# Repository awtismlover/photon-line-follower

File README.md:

<h1 align="center"> Photon1.0: Turbo Line Follower Robot</h1>

<div align="center">

<i>Loved the project? Please consider giving a Star ⭐️</i>

</div>

## ⭐️For now work in progres⭐️

> ### **Photon will be fast and light line follower robot with track optimalization.**

## Custom ESC

> ### **For the drive system Photon will use BLDC motors which will be driven by ESCs based on Escape32**

<div align="center">
  
</div>

## Hardware

- uC - STM32G474RET6
- drivers - Custom ESCs
- sensor - 12x KTIR0711S
- battery - 300mAh 3s LiPo
- wheels - Kyosho Mini Z
- motors - 1404 BLDC
- Bluetooth - HC-04

## Credits
> Photon uses custom BLDC based on neoxic's ESCape32 project
> https://github.com/neoxic/ESCape32

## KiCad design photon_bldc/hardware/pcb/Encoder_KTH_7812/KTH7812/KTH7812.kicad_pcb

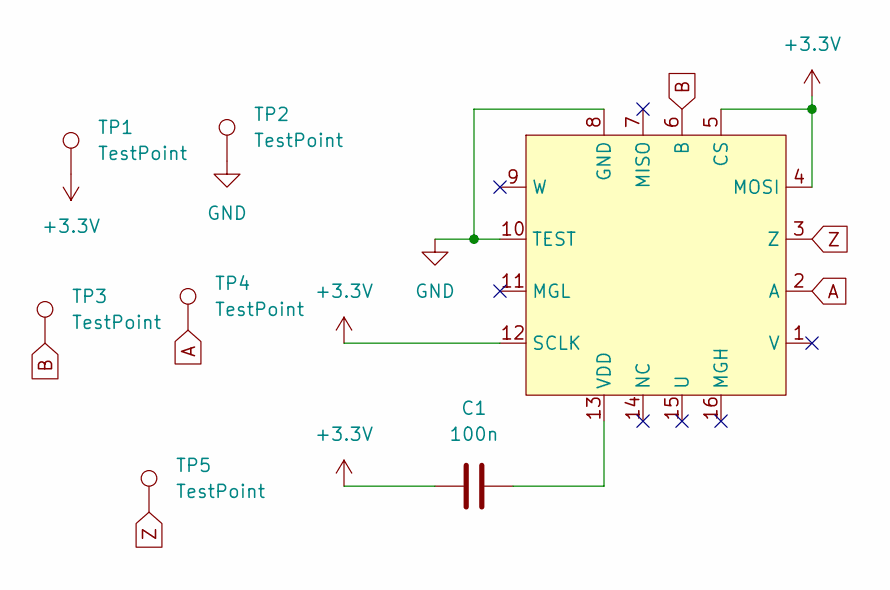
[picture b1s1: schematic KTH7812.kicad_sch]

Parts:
C1: 100n; C_0402_1005Metric
TP1, TP2, TP3, TP4, TP5: TestPoint; TestPoint_Pad_1.0x1.0mm
U1: KTH7812

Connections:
+3.3V: C1.1, TP1.1, U1.4 (MOSI), U1.5 (CS), U1.12 (SCLK)
A: TP4.1, U1.2 (A)
B: TP3.1, U1.6 (B)
GND: TP2.1, U1.8 (GND), U1.10 (TEST)
unnamed: C1.2, U1.13 (VDD)
Z: TP5.1, U1.3 (Z)

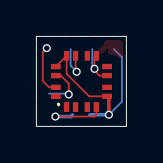
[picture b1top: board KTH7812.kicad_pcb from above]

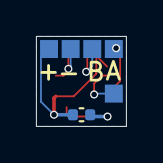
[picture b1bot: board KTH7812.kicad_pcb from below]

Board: 2 copper layers, 5.0 x 5.0 mm, 7 parts (6 on the bottom side), 6 nets.

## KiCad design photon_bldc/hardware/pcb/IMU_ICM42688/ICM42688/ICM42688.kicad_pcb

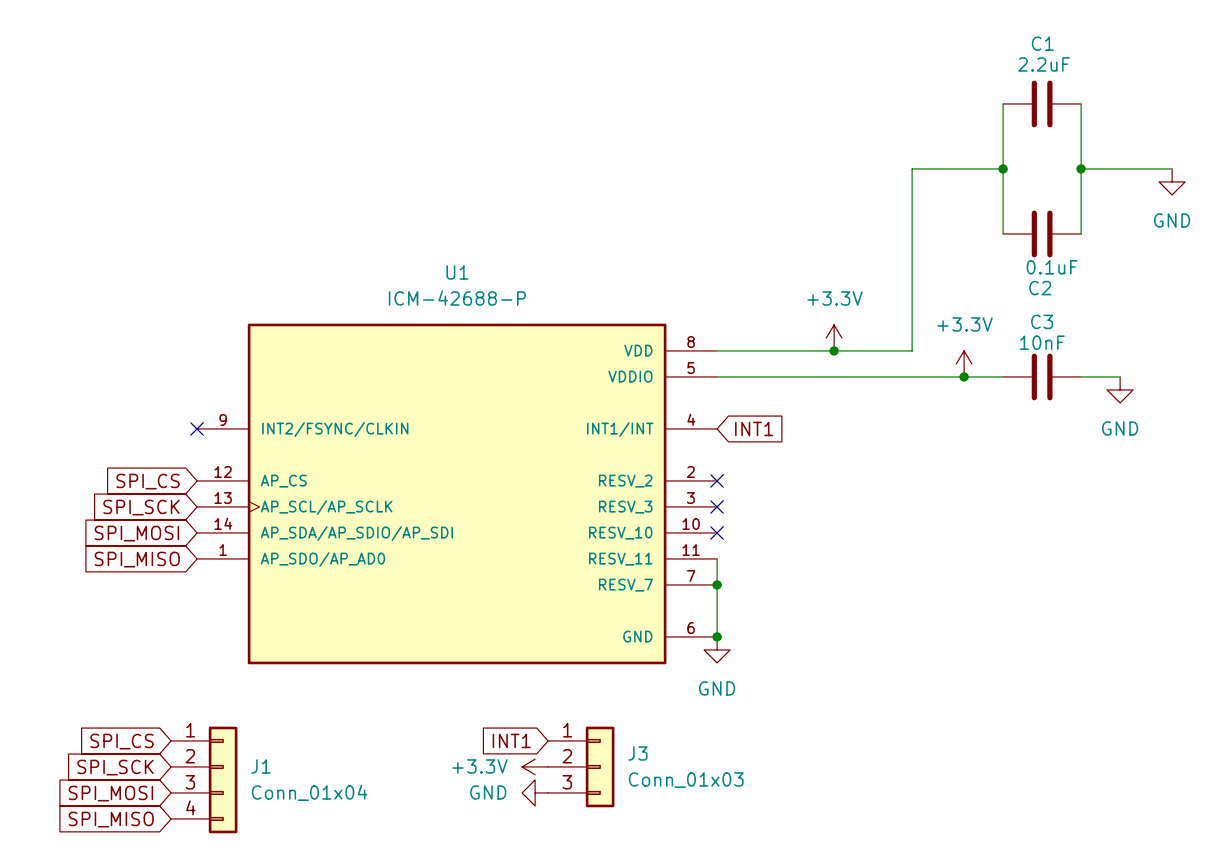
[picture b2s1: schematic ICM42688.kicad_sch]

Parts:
C1: 2.2uF; C_0402_1005Metric_Pad0.74x0.62mm_HandSolder
C2: 0.1uF; C_0402_1005Metric_Pad0.74x0.62mm_HandSolder
C3: 10nF; C_0402_1005Metric_Pad0.74x0.62mm_HandSolder
J1: Conn_01x04; 4_cable_pad
J3: Conn_01x03; 3_cable_pad
U1: ICM-42688-P; PQFN50P300X250X97-14N; PARTREV 1.2

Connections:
+3.3V: C1.2, C2.1, C3.1, J3.2, U1.5 (VDDIO), U1.8 (VDD)
GND: C1.1, C2.2, C3.2, J3.3, U1.6 (GND), U1.7 (RESV_7), U1.11 (RESV_11)
INT1: J3.1, U1.4 (INT1/INT)
SPI_CS: J1.1, U1.12 (AP_CS)
SPI_MISO: J1.4, U1.1 (AP_SDO/AP_AD0)
SPI_MOSI: J1.3, U1.14 (AP_SDA/AP_SDIO/AP_SDI)
SPI_SCK: J1.2, U1.13 (AP_SCL/AP_SCLK)

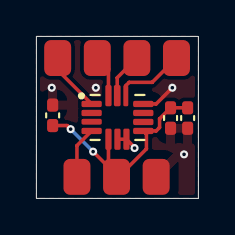
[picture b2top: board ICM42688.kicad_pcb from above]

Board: 2 copper layers, 9.0 x 9.0 mm, 6 parts (0 on the bottom side), 7 nets.

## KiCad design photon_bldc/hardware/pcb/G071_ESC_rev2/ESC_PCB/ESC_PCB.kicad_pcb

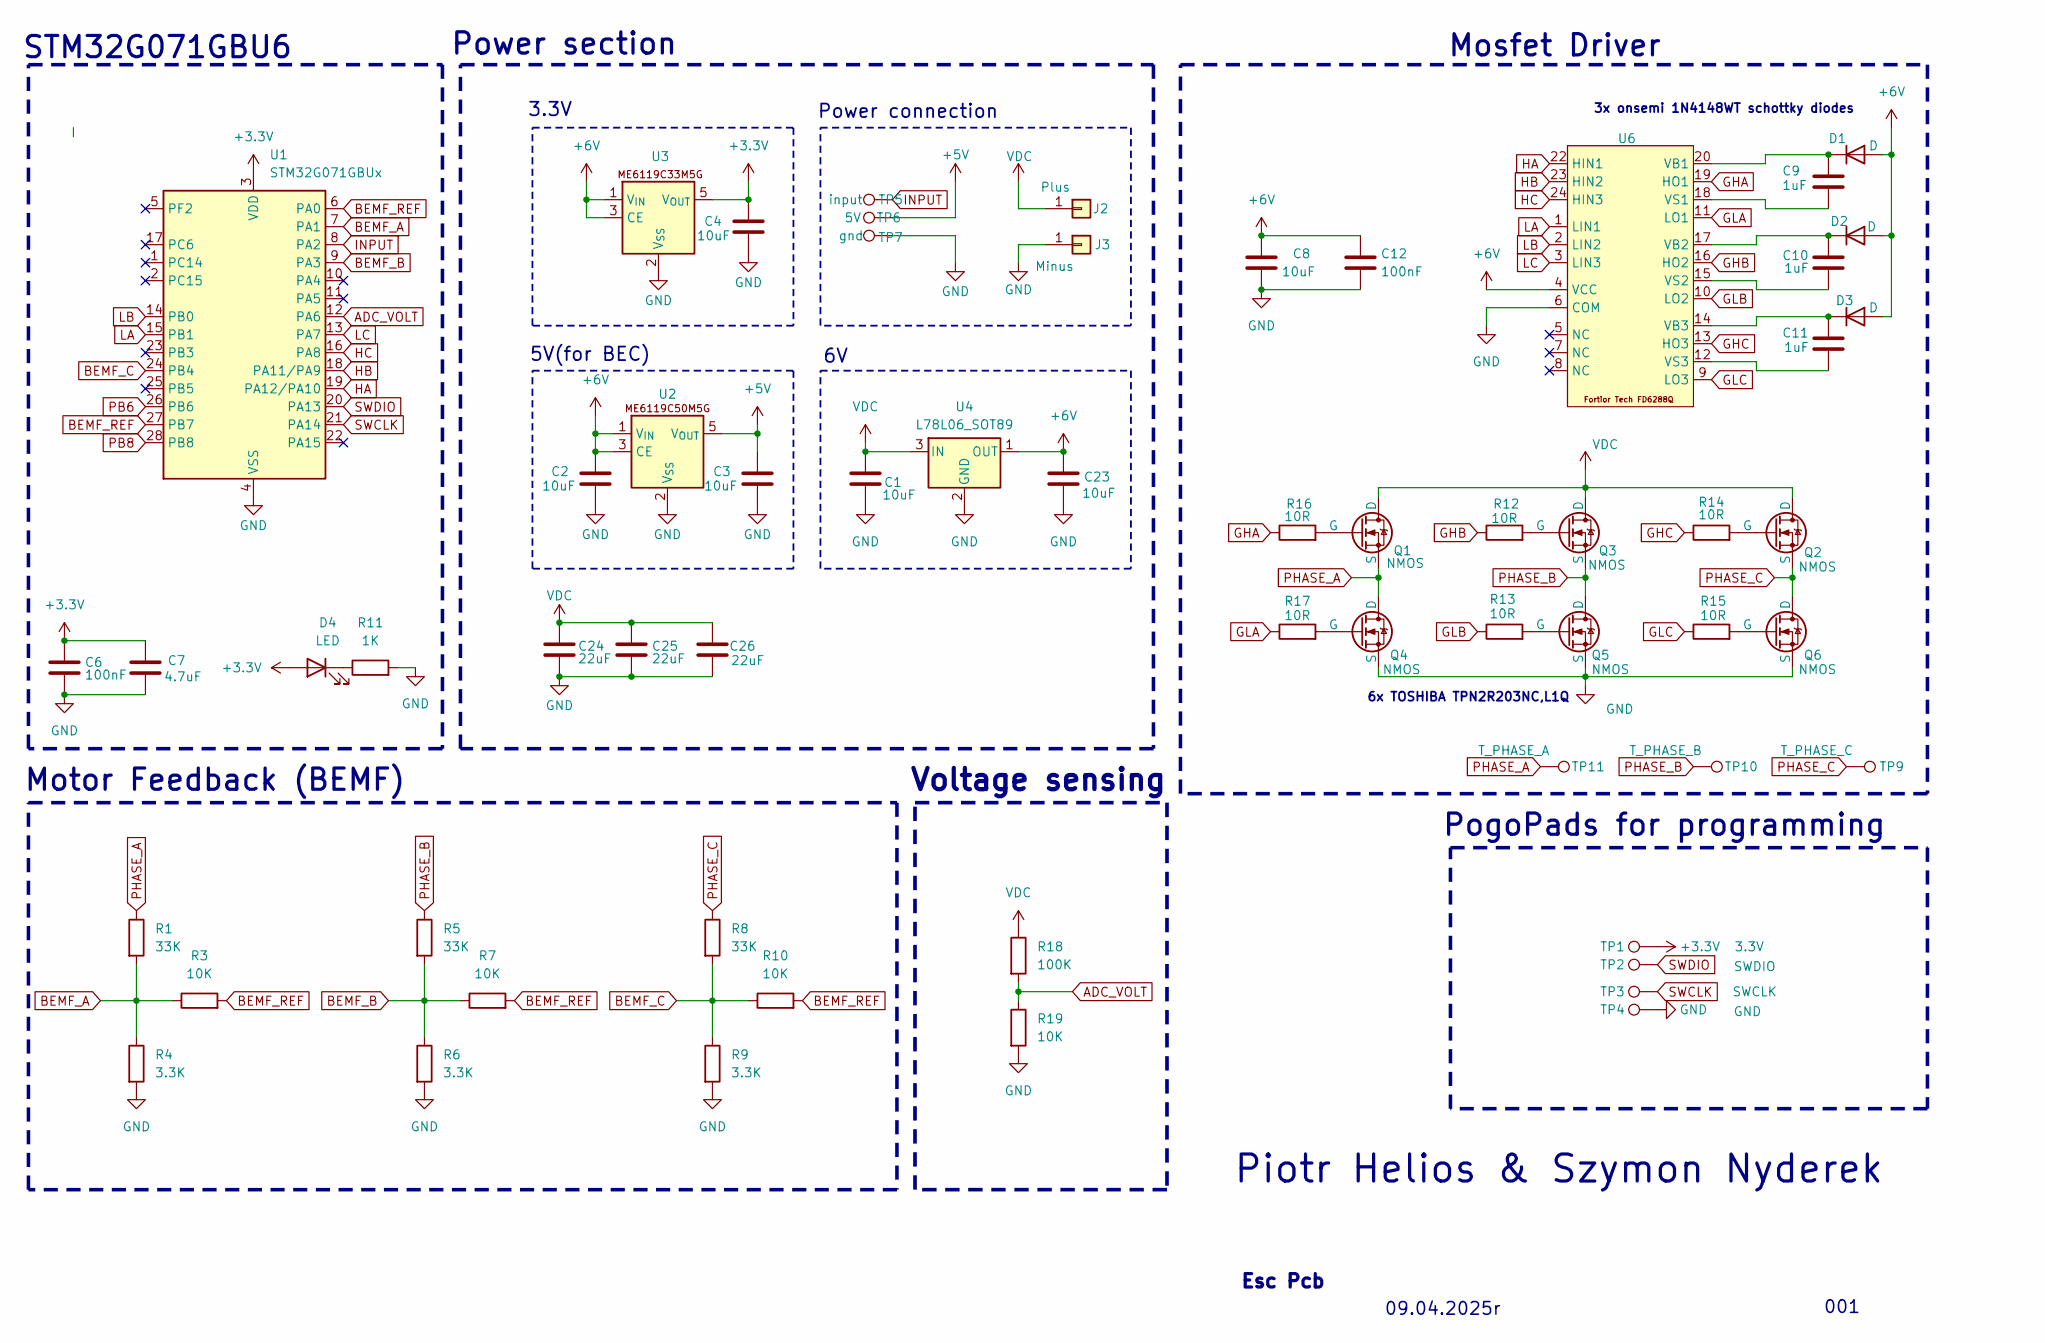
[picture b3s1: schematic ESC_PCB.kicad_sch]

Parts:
C1, C2, C3, C4: 10uF; C_0402_1005Metric_Pad0.74x0.62mm_HandSolder
C6, C12: 100nF; C_0402_1005Metric_Pad0.74x0.62mm_HandSolder
C7: 4.7uF; C_0402_1005Metric_Pad0.74x0.62mm_HandSolder
C8, C23: 10uF; C_0603_1608Metric_Pad1.08x0.95mm_HandSolder
C9, C10, C11: 1uF; C_0402_1005Metric_Pad0.74x0.62mm_HandSolder
C24, C25, C26: 22uF; C_0805_2012Metric_Pad1.18x1.45mm_HandSolder
D1, D2, D3: D; D_SOD-523
D4: LED; LED_0603_1608Metric_Pad1.05x0.95mm_HandSolder
J2: Plus; PowerPad
J3: Minus; PowerPad
Q1, Q2, Q3, Q4, Q5, Q6: NMOS; TRANS_TPHR8504PL_L1Q
R1, R5, R8: 33K; R_0402_1005Metric_Pad0.72x0.64mm_HandSolder
R3, R7, R10, R19: 10K; R_0402_1005Metric_Pad0.72x0.64mm_HandSolder
R4, R6, R9: 3.3K; R_0402_1005Metric_Pad0.72x0.64mm_HandSolder
R11: 1K; R_0402_1005Metric_Pad0.72x0.64mm_HandSolder
R12, R13, R14, R15, R16, R17: 10R; R_0402_1005Metric_Pad0.72x0.64mm_HandSolder
R18: 100K; R_0402_1005Metric_Pad0.72x0.64mm_HandSolder
TP1: 3.3V; TestPoint_Pad_D1.0mm
TP2: SWDIO; TestPoint_Pad_D1.0mm
TP3: SWCLK; TestPoint_Pad_D1.0mm
TP4: GND; TestPoint_Pad_D1.0mm
TP5: input; SolderWirePad_1x01_SMD_1x2mm
TP6: 5V; SolderWirePad_1x01_SMD_1x2mm
TP7: gnd; SolderWirePad_1x01_SMD_1x2mm
TP9: T_PHASE_C; PhasePad
TP10: T_PHASE_B; PhasePad
TP11: T_PHASE_A; PhasePad
U1: STM32G071GBUx; QFN-28_4x4mm_P0.5mm
U2, U3: SOT-23-5
U4: L78L06_SOT89; SOT-89-3
U6: QFN50P400X400X90-25N

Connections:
+3.3V: C4.1, C6.1, C7.1, D4.2 (A), TP1.1, U1.3 (VDD), U3.5 (V_{OUT})
+5V: C3.1, TP6.1, U2.5 (V_{OUT})
+6V: C2.1, C8.1, C12.1, C23.1, D1.2 (A), D2.2 (A), D3.2 (A), U2.1 (V_{IN}), U2.3 (CE), U3.1 (V_{IN}), U3.3 (CE), U4.1 (OUT), U6.4 (VCC)
ADC_VOLT: R18.2, R19.1, U1.12 (PA6)
BEMF_A: R1.2, R3.1, R4.1, U1.7 (PA1)
BEMF_B: R5.2, R6.1, R7.1, U1.9 (PA3)
BEMF_C: R8.2, R9.1, R10.1, U1.24 (PB4)
BEMF_REF: R3.2, R7.2, R10.2, U1.6 (PA0), U1.27 (PB7)
GHA: R16.1, U6.19 (HO1)
GHB: R12.1, U6.16 (HO2)
GHC: R14.1, U6.13 (HO3)
GLA: R17.1, U6.11 (LO1)
GLB: R13.1, U6.10 (LO2)
GLC: R15.1, U6.9 (LO3)
GND: C1.2, C2.2, C3.2, C4.2, C6.2, C7.2, C8.2, C12.2, C23.2, C24.2, C25.2, C26.2, J3.1, Q4.3 (S), Q5.3 (S), Q6.3 (S), R4.2, R6.2, R9.2, R11.2, R19.2, TP4.1, TP7.1, U1.4 (VSS), U2.2 (V_{SS}), U3.2 (V_{SS}), U4.2 (GND), U6.6 (COM); also elsewhere on the board
HA: U1.19 (PA12/PA10), U6.22 (HIN1)
HB: U1.18 (PA11/PA9), U6.23 (HIN2)
HC: U1.16 (PA8), U6.24 (HIN3)
INPUT: TP5.1, U1.8 (PA2)
LA: U1.15 (PB1), U6.1 (LIN1)
LB: U1.14 (PB0), U6.2 (LIN2)
LC: U1.13 (PA7), U6.3 (LIN3)
unnamed: C9.1, D1.1 (K), U6.20 (VB1)
unnamed: C10.1, D2.1 (K), U6.17 (VB2)
unnamed: C11.1, D3.1 (K), U6.14 (VB3)
unnamed: D4.1 (K), R11.1
unnamed: Q1.2 (G), R16.2
unnamed: Q2.2 (G), R14.2
unnamed: Q3.2 (G), R12.2
unnamed: Q4.2 (G), R17.2
unnamed: Q5.2 (G), R13.2
unnamed: Q6.2 (G), R15.2
unnamed: C9.2, U6.18 (VS1)
unnamed: C10.2, U6.15 (VS2)
unnamed: C11.2, U6.12 (VS3)
PB6: U1.26 (PB6)
PB8: U1.28 (PB8)
PHASE_A: Q1.3 (S), Q4.1 (D), R1.1, TP11.1
PHASE_B: Q3.3 (S), Q5.1 (D), R5.1, TP10.1
PHASE_C: Q2.3 (S), Q6.1 (D), R8.1, TP9.1
SWCLK: TP3.1, U1.21 (PA14)
SWDIO: TP2.1, U1.20 (PA13)
VDC: C1.1, C24.1, C25.1, C26.1, J2.1, Q1.1 (D), Q2.1 (D), Q3.1 (D), R18.1, U4.3 (IN); also elsewhere on the board

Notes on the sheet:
Power section
001
3x onsemi 1N4148WT schottky diodes
3.3V
Esc Pcb
5V(for BEC)
Piotr Helios & Szymon Nyderek
Voltage sensing
Motor Feedback (BEMF)
Mosfet Driver
Power connection
STM32G071GBU6
PogoPads for programming
6x TOSHIBA TPN2R203NC,L1Q
09.04.2025r

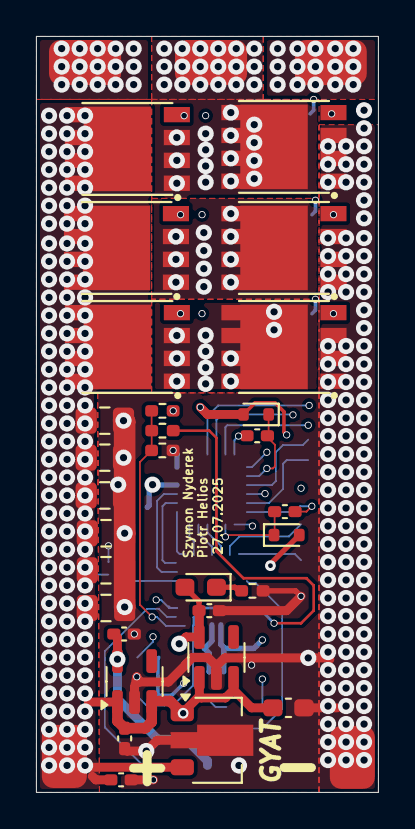
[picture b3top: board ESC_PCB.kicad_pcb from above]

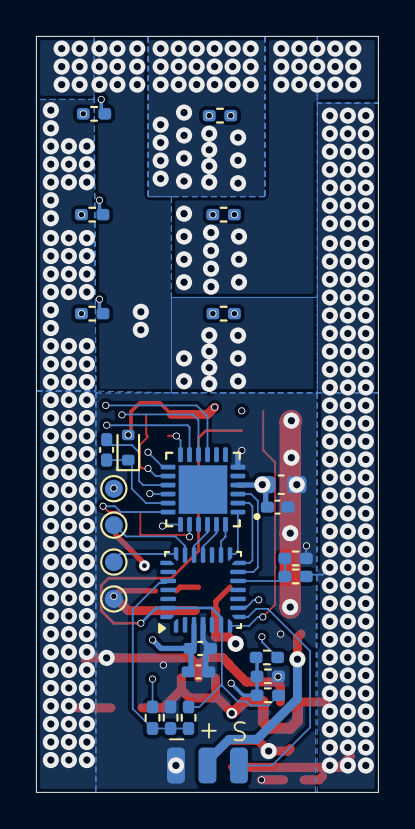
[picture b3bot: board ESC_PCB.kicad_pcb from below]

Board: 6 copper layers, 19.0 x 42.0 mm, 63 parts (29 on the bottom side), 41 nets.

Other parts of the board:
C24#2, C25#2, C26#2: 22uF; C_0805_2012Metric_Pad1.18x1.45mm_HandSolder

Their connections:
GND: C24#2.2, C25#2.2, C26#2.2; also elsewhere on the board
VDC: C24#2.1, C25#2.1, C26#2.1; also elsewhere on the board

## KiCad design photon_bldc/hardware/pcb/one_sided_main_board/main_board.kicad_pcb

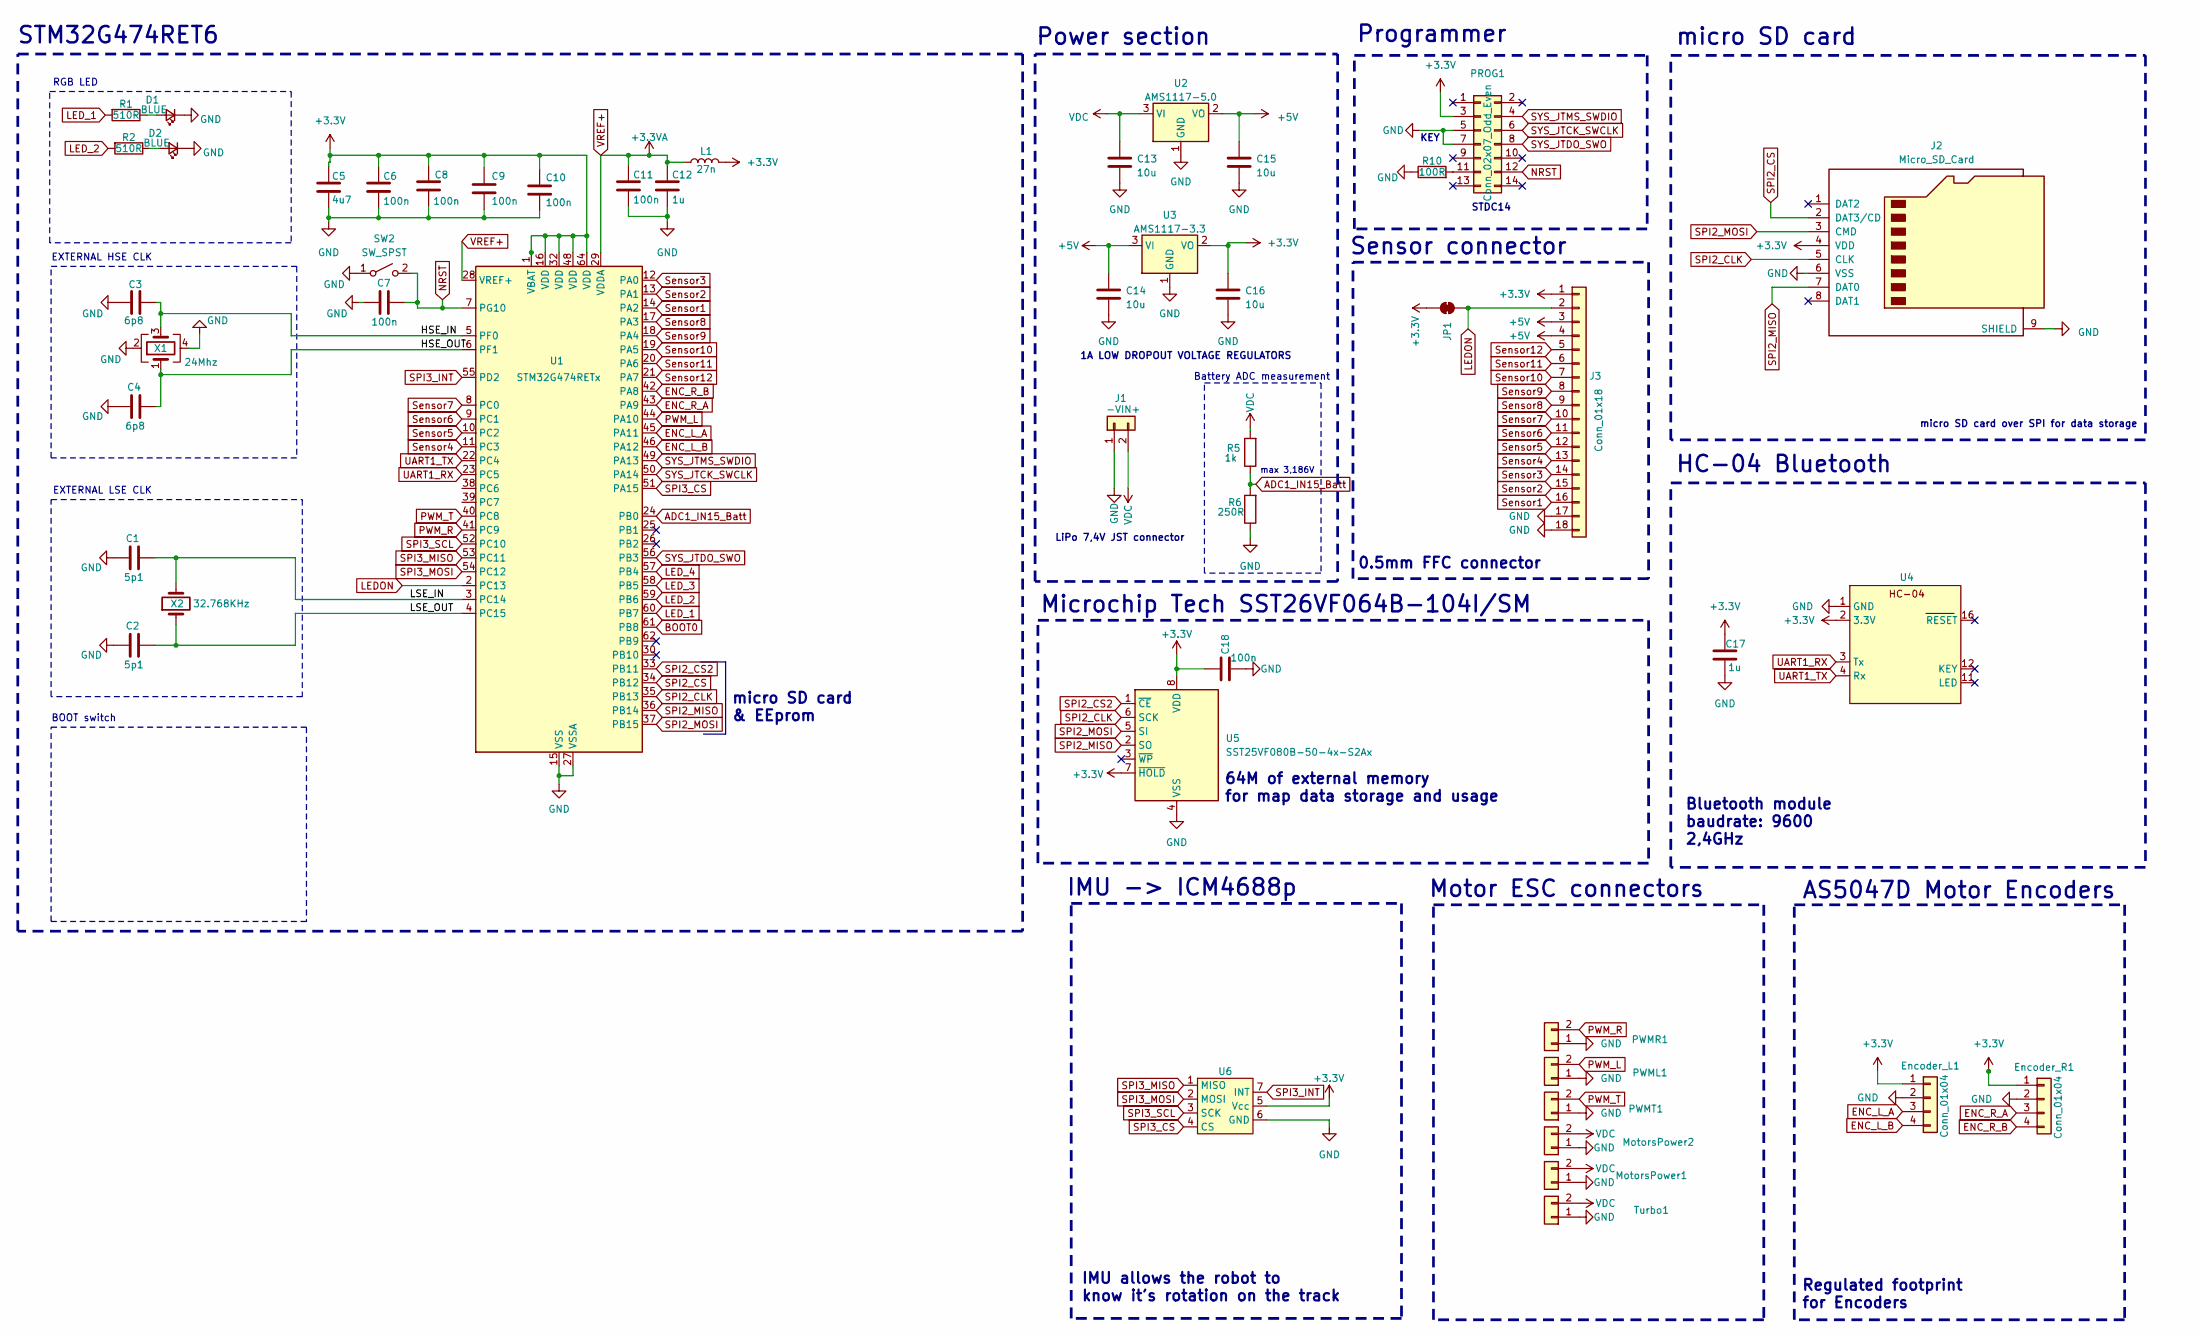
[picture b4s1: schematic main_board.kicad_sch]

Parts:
C1, C2: 5p1; C_0603_1608Metric
C3, C4: 6p8; C_0603_1608Metric
C5: 4u7; C_0603_1608Metric
C6, C7, C8, C9, C10, C11, C18: 100n; C_0603_1608Metric
C12, C17: 1u; C_0603_1608Metric
C13, C14, C15, C16: 10u; C_0603_1608Metric
D1, D2: BLUE; LED_0603_1608Metric; LCSC Part # C72041
Encoder_L1: Conn_01x04; JST_SH_SM04B-SRSS-TB_1x04-1MP_P1.00mm_Horizontal
Encoder_R1: Conn_01x04; JST_SH_SM04B-SRSS-TB_1x04-1MP_P1.00mm_Horizontal
J1: -VIN+; AMASS_XT30U-F_1x02_P5.0mm_Vertical
J2: Micro_SD_Card; SdCard
J3: Conn_01x18; Hirose_FH12-18S-0.5SH_1x18-1MP_P0.50mm_Horizontal
JP1: SolderJumper_2_Bridged; SolderJumper-2_P1.3mm_Bridged2Bar_RoundedPad1.0x1.5mm
L1: 27n; L_0603_1608Metric
MotorsPower1, MotorsPower2: Conn_01x02; PowerConn
PROG1: Conn_02x07_Odd_Even; PinHeader_2x07_P1.27mm_Vertical_SMD
PWML1: Conn_01x02; JST_SH_SM02B-SRSS-TB_1x02-1MP_P1.00mm_Horizontal
PWMR1: Conn_01x02; JST_SH_SM02B-SRSS-TB_1x02-1MP_P1.00mm_Horizontal
PWMT1: Conn_01x02; JST_SH_SM02B-SRSS-TB_1x02-1MP_P1.00mm_Horizontal
R1, R2: 510R; R_0603_1608Metric
R5: 1k; R_0603_1608Metric
R6: 250R; R_0603_1608Metric
R10: 100R; R_0603_1608Metric
SW2: SW_SPST; SW_SPST_CK_RS282G05A3
Turbo1: Conn_01x02; PowerConn
U1: STM32G474RETx; LQFP-64_10x10mm_P0.5mm
U2: AMS1117-5.0; SOT-223-3_TabPin2
U3: AMS1117-3.3; SOT-223-3_TabPin2
U4: HC-04
U5: SST25VF080B-50-4x-S2Ax; SOIC-8_5.275x5.275mm_P1.27mm
U6: ICM_MOUNT
X1: 24Mhz; Crystal_SMD_2016-4Pin_2.0x1.6mm
X2: 32.768KHz; Crystal_SMD_3215-2Pin_3.2x1.5mm

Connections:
+3.3V: C5.1, C6.1, C8.1, C9.1, C10.1, C16.1, C17.1, C18.1, Encoder_L1.1, Encoder_R1.1, J2.4 (VDD), J3.1, JP1.2 (B), L1.2, PROG1.3, U1.1 (VBAT), U1.16 (VDD), U1.32 (VDD), U1.48 (VDD), U1.64 (VDD), U3.2 (VO), U4.2 (3.3V), U5.7 (~HOLD), U5.8 (VDD), U6.5 (Vcc); also elsewhere on the board
+5V: C14.1, C15.1, J3.3, J3.4, U2.2 (VO), U3.3 (VI)
/HSE_IN: C3.2, U1.5 (PF0), X1.3
/HSE_OUT: C4.2, U1.6 (PF1), X1.1
/LSE_IN: C1.2, U1.3 (PC14), X2.2
/LSE_OUT: C2.2, U1.4 (PC15), X2.1
ADC1_IN15_Batt: R5.1, R6.2, U1.24 (PB0)
BOOT0: U1.61 (PB8)
ENC_L_A: Encoder_L1.3, U1.45 (PA11)
ENC_L_B: Encoder_L1.4, U1.46 (PA12)
ENC_R_A: Encoder_R1.3, U1.43 (PA9)
ENC_R_B: Encoder_R1.4, U1.42 (PA8)
GND: C1.1, C2.1, C3.1, C4.1, C5.2, C6.2, C7.1, C8.2, C9.2, C10.2, C11.2, C12.2, C13.2, C14.2, C15.2, C16.2, C17.2, C18.2, D1.1 (K), D2.1 (K), Encoder_L1.2, Encoder_R1.2, J1.1, J2.6 (VSS), J2.9 (SHIELD), J2.SH, J3.17, J3.18, J3.MP, MotorsPower1.1, MotorsPower2.1, PROG1.5, PROG1.7, PWML1.1, PWMR1.1, PWMT1.1, R6.1, R10.1, SW2.1 (A), Turbo1.1, U1.15 (VSS), U1.27 (VSSA), U1.31 (VSS), U1.47 (VSS), U1.63 (VSS), U2.1 (GND), U3.1 (GND), U4.1 (GND), U5.4 (VSS), U6.6 (GND), X1.2, X1.4
LEDON: J3.2, JP1.1 (A), U1.2 (PC13); also elsewhere on the board
LED_1: R1.2, U1.60 (PB7)
LED_2: R2.2, U1.59 (PB6)
LED_3: U1.58 (PB5)
LED_4: U1.57 (PB4)
NRST: C7.2, PROG1.12, SW2.2 (B), U1.7 (PG10)
unnamed: D1.2 (A), R1.1
unnamed: D2.2 (A), R2.1
unnamed: PROG1.11, R10.2
PWM_L: PWML1.2, U1.44 (PA10)
PWM_R: PWMR1.2, U1.41 (PC9)
PWM_T: PWMT1.2, U1.40 (PC8)
SPI2_CLK: J2.5 (CLK), U1.35 (PB13), U5.6 (SCK)
SPI2_CS: J2.2 (DAT3/CD), U1.34 (PB12)
SPI2_CS2: U1.33 (PB11), U5.1 (~CE)
SPI2_MISO: J2.7 (DAT0), U1.36 (PB14), U5.2 (SO)
SPI2_MOSI: J2.3 (CMD), U1.37 (PB15), U5.5 (SI)
SPI3_CS: U1.51 (PA15), U6.4 (CS)
SPI3_INT: U1.55 (PD2), U6.7 (INT)
SPI3_MISO: U1.53 (PC11), U6.1 (MISO)
SPI3_MOSI: U1.54 (PC12), U6.2 (MOSI)
SPI3_SCL: U1.52 (PC10), U6.3 (SCK)
SYS_JTCK_SWCLK: PROG1.6, U1.50 (PA14)
SYS_JTDO_SWO: PROG1.8, U1.56 (PB3)
SYS_JTMS_SWDIO: PROG1.4, U1.49 (PA13)
Sensor1: J3.16, U1.14 (PA2)
Sensor2: J3.15, U1.13 (PA1)
Sensor3: J3.14, U1.12 (PA0)
Sensor4: J3.13, U1.11 (PC3)
Sensor5: J3.12, U1.10 (PC2)
Sensor6: J3.11, U1.9 (PC1)
Sensor7: J3.10, U1.8 (PC0)
Sensor8: J3.9, U1.17 (PA3)
Sensor9: J3.8, U1.18 (PA4)
Sensor10: J3.7, U1.19 (PA5)
Sensor11: J3.6, U1.20 (PA6)
Sensor12: J3.5, U1.21 (PA7)
UART1_RX: U1.23 (PC5), U4.3 (Tx)
UART1_TX: U1.22 (PC4), U4.4 (Rx)
VDC: C13.1, J1.2, MotorsPower1.2, MotorsPower2.2, R5.2, Turbo1.2, U2.3 (VI)
VREF+: C11.1, C12.1, L1.1, U1.28 (VREF+), U1.29 (VDDA)

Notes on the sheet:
Bluetooth module baudrate: 9600 2,4GHz
Regulated footprint for Encoders
RGB LED
HC-04 Bluetooth
EXTERNAL LSE CLK
max 3,186V
EXTERNAL HSE CLK
micro SD card & EEprom
LiPo 7,4V JST connector
IMU allows the robot to know it's rotation on the track
IMU -> ICM4688p
64M of external memory for map data storage and usage
1A LOW DROPOUT VOLTAGE REGULATORS
Motor ESC connectors
micro SD card
Sensor connector
STDC14
AS5047D Motor Encoders
BOOT switch
Microchip Tech SST26VF064B-104I/SM
Power section
KEY
0.5mm FFC connector
Programmer
STM32G474RET6
micro SD card over SPI for data storage
Battery ADC measurement

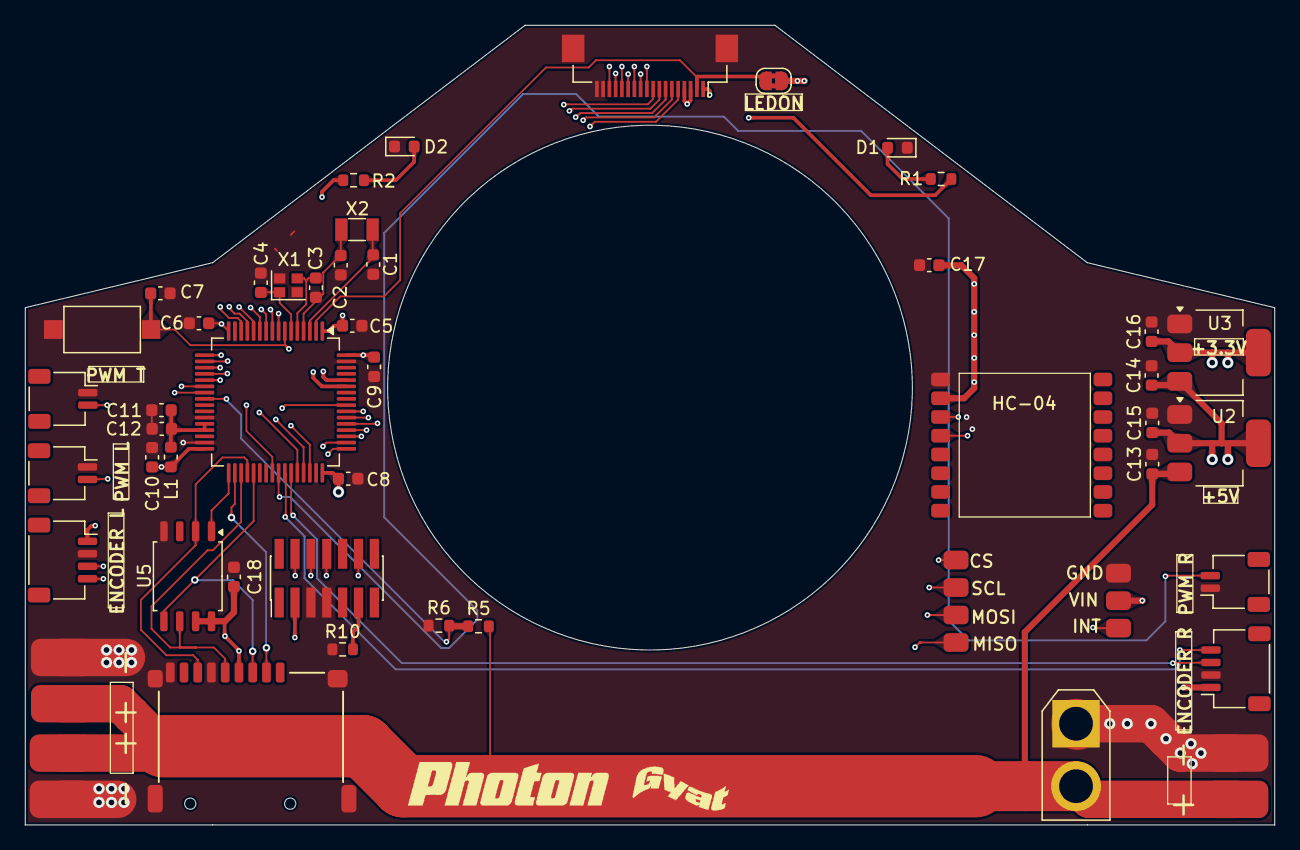
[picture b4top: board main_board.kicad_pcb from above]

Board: 4 copper layers, 100.0 x 64.0 mm, 48 parts (0 on the bottom side), 51 nets.

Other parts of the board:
LEDON: SolderJumper_2_Bridged; SolderJumper-2_P1.3mm_Bridged2Bar_RoundedPad1.0x1.5mm

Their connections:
+3.3V: LEDON.2 (B); also elsewhere on the board
LEDON: LEDON.1 (A); also elsewhere on the board

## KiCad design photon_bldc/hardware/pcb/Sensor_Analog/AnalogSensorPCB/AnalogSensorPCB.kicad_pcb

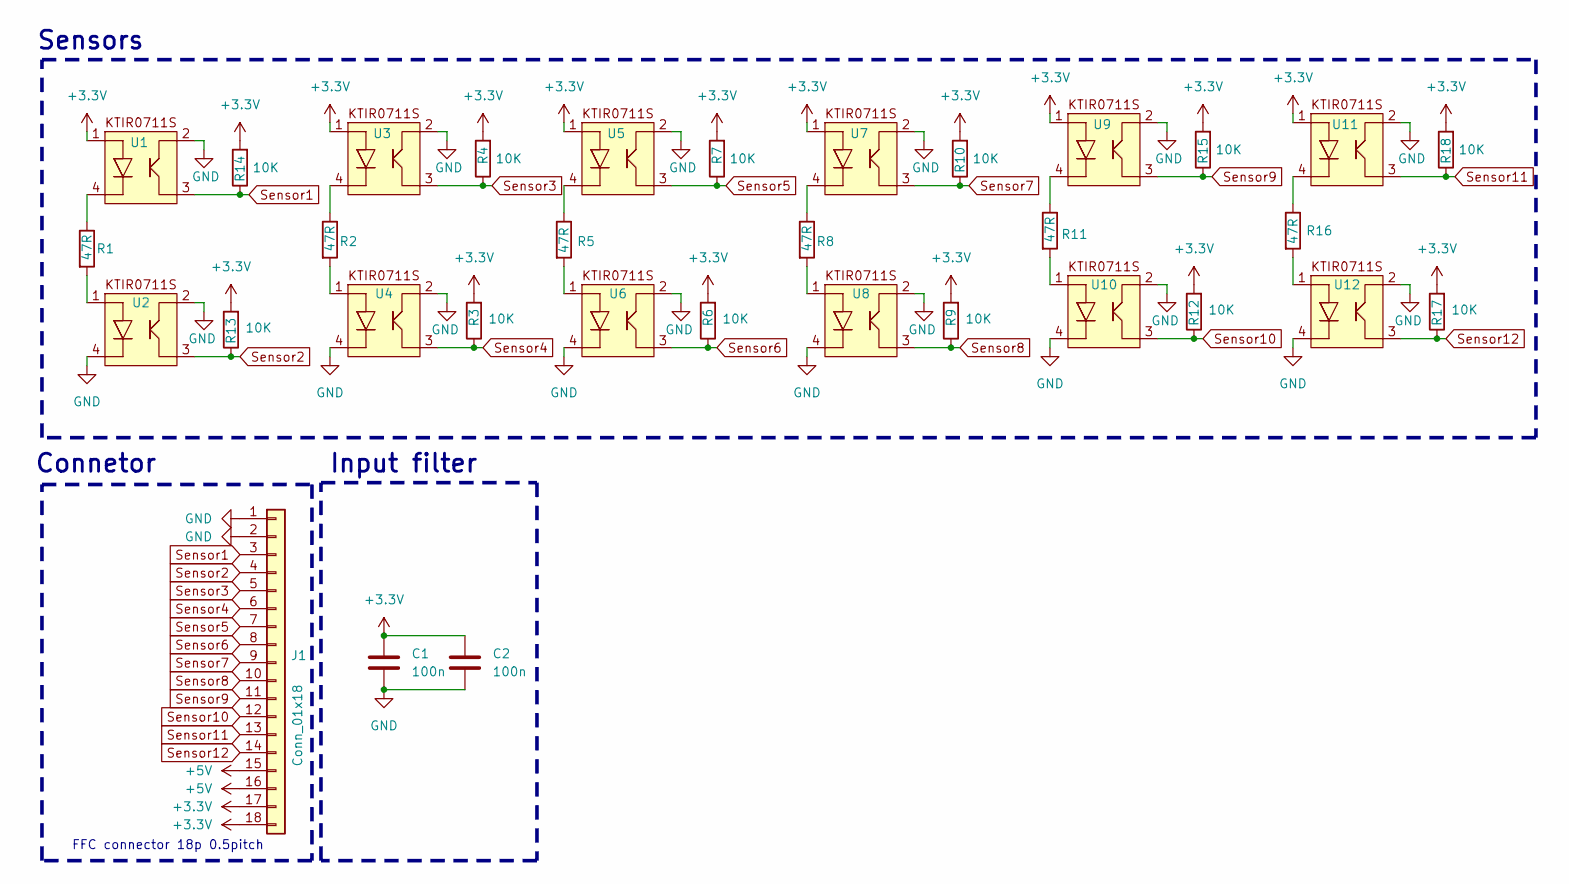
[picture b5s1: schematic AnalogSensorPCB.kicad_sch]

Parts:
C1, C2: 100n; C_0402_1005Metric_Pad0.74x0.62mm_HandSolder
J1: Conn_01x18; Hirose_FH12-18S-0.5SH_1x18-1MP_P0.50mm_Horizontal
R1, R2, R5, R8, R11, R16: 47R; R_0603_1608Metric_Pad0.98x0.95mm_HandSolder
R3, R4, R6, R7, R9, R10, R12, R13, R14, R15, R17, R18: 10K; R_0402_1005Metric_Pad0.72x0.64mm_HandSolder
U1, U2, U3, U4, U5, U6, U7, U8, U9, U10, U11, U12: KTIR0711S

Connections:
+3.3V: C1.1, C2.1, J1.17, J1.18, R3.2, R4.2, R6.2, R7.2, R9.2, R10.2, R12.2, R13.2, R14.2, R15.2, R17.2, R18.2, U1.1, U3.1, U5.1, U7.1, U9.1, U11.1
+5V: J1.15, J1.16
GND: C1.2, C2.2, J1.1, J1.2, J1.MP, U1.2, U2.2, U2.4, U3.2, U4.2, U4.4, U5.2, U6.2, U6.4, U7.2, U8.2, U8.4, U9.2, U10.2, U10.4, U11.2, U12.2, U12.4
unnamed: R1.1, U1.4
unnamed: R1.2, U2.1
unnamed: R2.1, U3.4
unnamed: R2.2, U4.1
unnamed: R5.1, U5.4
unnamed: R5.2, U6.1
unnamed: R8.1, U7.4
unnamed: R8.2, U8.1
unnamed: R11.1, U9.4
unnamed: R11.2, U10.1
unnamed: R16.1, U11.4
unnamed: R16.2, U12.1
Sensor1: J1.3, R14.1, U1.3
Sensor2: J1.4, R13.1, U2.3
Sensor3: J1.5, R4.1, U3.3
Sensor4: J1.6, R3.1, U4.3
Sensor5: J1.7, R7.1, U5.3
Sensor6: J1.8, R6.1, U6.3
Sensor7: J1.9, R10.1, U7.3
Sensor8: J1.10, R9.1, U8.3
Sensor9: J1.11, R15.1, U9.3
Sensor10: J1.12, R12.1, U10.3
Sensor11: J1.13, R18.1, U11.3
Sensor12: J1.14, R17.1, U12.3

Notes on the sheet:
FFC connector 18p 0.5pitch
Input filter
Connetor
Sensors

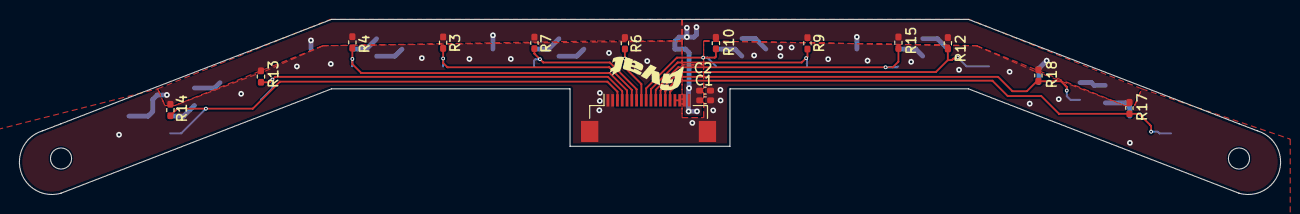
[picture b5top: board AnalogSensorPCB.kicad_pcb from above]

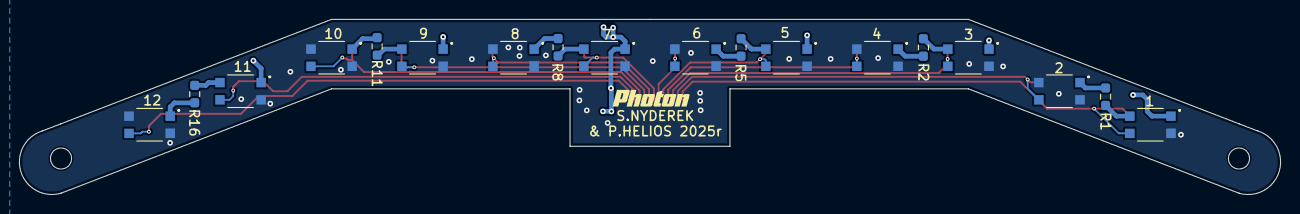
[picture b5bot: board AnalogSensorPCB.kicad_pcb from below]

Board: 2 copper layers, 131.7 x 18.3 mm, 33 parts (18 on the bottom side), 27 nets.

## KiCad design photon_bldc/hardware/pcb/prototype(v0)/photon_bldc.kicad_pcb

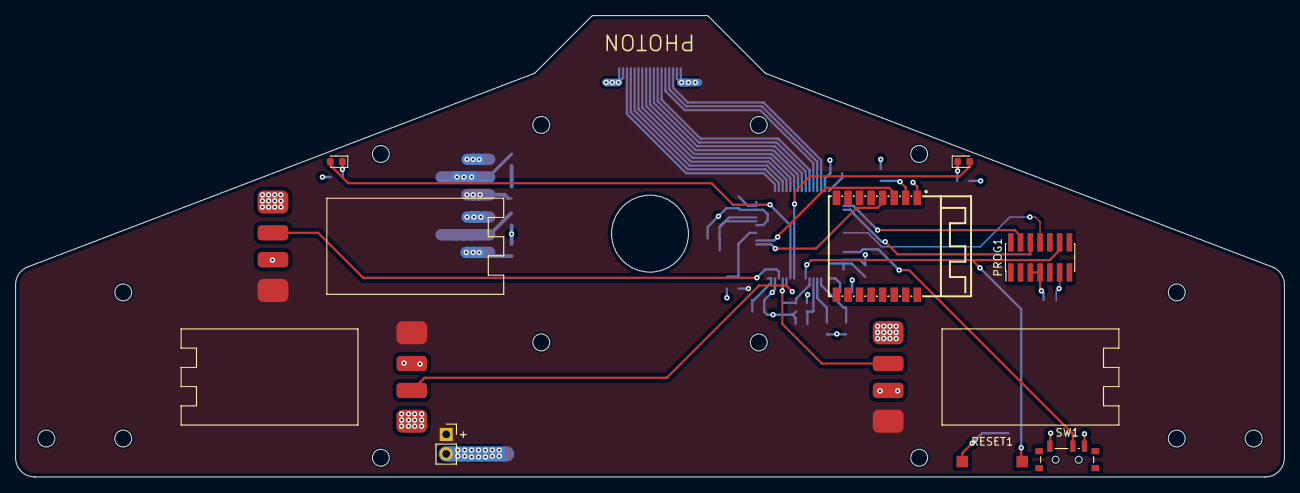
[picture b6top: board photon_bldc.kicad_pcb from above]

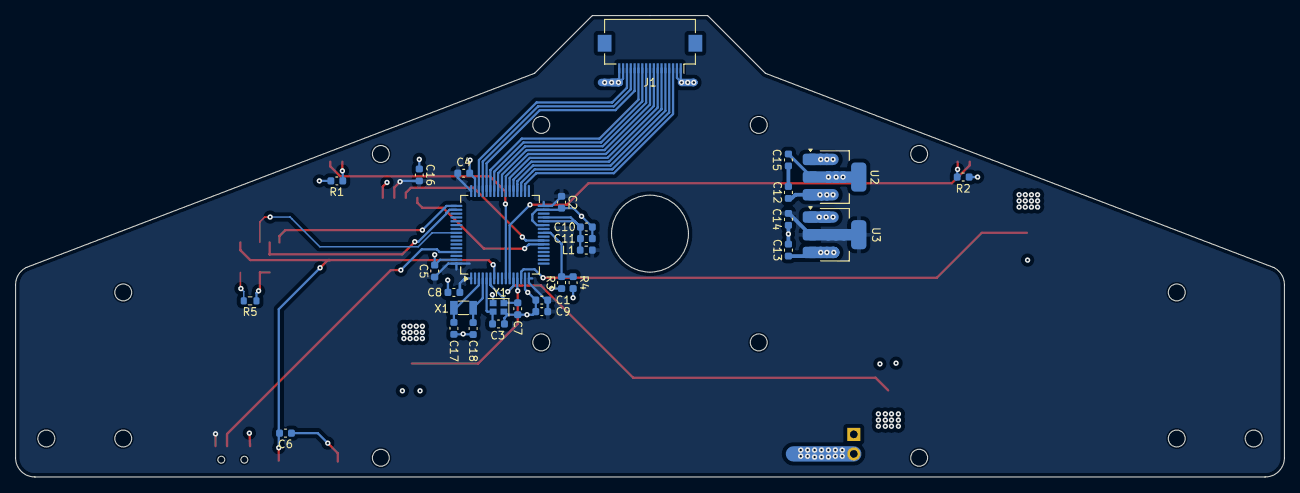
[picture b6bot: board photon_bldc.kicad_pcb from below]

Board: 4 copper layers, 165.0 x 60.0 mm, 37 parts (30 on the bottom side), 36 nets.

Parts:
C1: 4u7; C_0603_1608Metric
C2, C4, C5, C6, C8, C9, C11: 100n; C_0603_1608Metric
C3, C7: 6p8; C_0603_1608Metric
C10: 1u; C_0603_1608Metric
C12, C13, C14, C15: 10u; C_0603_1608Metric
C16: 0.1u; C_0603_1608Metric
C17, C18: 5p1; C_0603_1608Metric
D1, D2: LED; LED_0603_1608Metric
J1: Conn_01x17; Hirose_FH12-17S-0.5SH_1x17-1MP_P0.50mm_Horizontal
L1: 27nH; L_0603_1608Metric
PROG1: Conn_02x07_Odd_Even; PinHeader_2x07_P1.27mm_Vertical_SMD
R1, R2: 510; C_0603_1608Metric
R3: 330K; C_0603_1608Metric
R4: 200K; C_0603_1608Metric
R5: 100R; R_0603_1608Metric
RESET1: SW_SPST; SW_SPST_CK_RS282G05A3
SW1: SW_DPDT_x2; SW_SPDT_PCM12
U1: STM32G474RBTx; LQFP-64_10x10mm_P0.5mm
U2: LM1117MP-5.0; SOT-223-3_TabPin2
U3: LM1117MP-3.3; SOT-223-3_TabPin2
U4: HC-04S; hc-04
VIN1: Conn_01x02; PinSocket_1x02_P2.54mm_Vertical
X1: 32.768KHz; Crystal_SMD_3215-2Pin_3.2x1.5mm
Y1: Crystal_GND24; Crystal_SMD_2016-4Pin_2.0x1.6mm

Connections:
+3.3V: C1.1, C2.1, C4.1, C5.1, C8.1, C9.1, C14.1, C16.2, L1.1, SW1.3 (C), U1.1 (VBAT), U1.16 (VDD), U1.32 (VDD), U1.48 (VDD), U1.64 (VDD), U3.2 (VO), U4.2 (VCC)
+5V: C13.1, C15.1, J1.1, J1.2, U2.2 (VO), U3.3 (VI)
/HSE_IN: C3.1, U1.5 (PF0), Y1.3
/HSE_OUT: C7.1, U1.6 (PF1), Y1.1
/LSE_IN: C17.2, U1.3 (PC14), X1.2
/LSE_OUT: C18.2, U1.4 (PC15), X1.1
ADC: R3.2, R4.1, U1.25 (PB1)
BOOT0: SW1.2 (B), U1.61 (PB8)
GND: C1.2, C2.2, C3.2, C4.2, C5.2, C6.1, C7.2, C8.2, C9.2, C10.2, C11.2, C13.2, C14.2, C16.1, C17.1, C18.1, J1.16, J1.17, PROG1.5, PROG1.7, R1.2, R2.2, R4.2, R5.1, RESET1.1 (A), SW1.1 (A), U1.15 (VSS), U1.27 (VSSA), U1.31 (VSS), U1.47 (VSS), U1.63 (VSS), U2.1 (GND), U3.1 (GND), U4.1 (GND), VIN1.2, Y1.2, Y1.4
LED1: D2.2 (A), U1.11 (PC3)
LED2: D1.2 (A), U1.10 (PC2)
LEDON: J1.15, U1.46 (PA12)
NRST: C6.2, PROG1.12, RESET1.2 (B), U1.7 (PG10)
unnamed: C12.2, C15.2
unnamed: D1.1 (K), R1.1
unnamed: D2.1 (K), R2.1
unnamed: PROG1.11, R5.2
PC4: U1.22 (PC4), U4.4 (RXD)
PC5: U1.23 (PC5), U4.3 (TXD)
SENSOR1: J1.14, U1.45 (PA11)
SENSOR2: J1.13, U1.44 (PA10)
SENSOR3: J1.12, U1.43 (PA9)
SENSOR4: J1.11, U1.42 (PA8)
SENSOR5: J1.10, U1.41 (PC9)
SENSOR6: J1.9, U1.40 (PC8)
SENSOR7: J1.8, U1.39 (PC7)
SENSOR8: J1.7, U1.38 (PC6)
SENSOR9: J1.6, U1.37 (PB15)
SENSOR10: J1.5, U1.36 (PB14)
SENSOR11: J1.4, U1.35 (PB13)
SENSOR12: J1.3, U1.34 (PB12)
SYS_JTCK_SWCLK: PROG1.6, U1.50 (PA14)
SYS_JTDO_SWO: PROG1.8, U1.56 (PB3)
SYS_JTMS_SWDIO: PROG1.4, U1.49 (PA13)
VDC: C12.1, R3.1, U2.3 (VI), VIN1.1
VREF+: C10.1, C11.1, L1.2, U1.28 (VREF+), U1.29 (VDDA)

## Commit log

2025-03-23 Small updates to PCB
2025-04-06 begining of ESC pcb
2025-04-08 g071
2025-04-08 ESC schemat continued
2025-04-09 jjjju
2025-04-09 Mosfet footprints Added
2025-04-10 imjimi
2025-04-10 mimi
2025-04-10 10.04.2025
2025-04-10 jjkjk
2025-04-11 11.04.2025
2025-04-11 11.04.2025-1
2025-04-11 sdfsdfgsdffgsdfsdsd
2025-04-11 11.04.2025-2
2025-04-11 gugui
2025-04-14 14.04.2025r
2025-04-15 15.04.2025
2025-04-15 15.04.2025-2
2025-04-16 16.04.2025r
2025-04-16 sgsfgsgs
2025-04-16 jgguighuugi
2025-04-16 uiyu
2025-04-16 17.04.2025r-3
2025-04-17 17.04.2025
2025-04-20 ojjojio
2025-04-20 21.04.2025
2025-04-20 21.03.2025r-2
2025-04-22 22.04.2025
2025-04-24 24.04.2025r
2025-04-28 28.04.2025
2025-04-28 29.04.25
2025-05-02 2.05
2025-05-05 6.05.25
2025-05-06 7.05.2025r
2025-05-06 07.05.02025
2025-05-07 jknj
2025-05-07 jijjio
2025-05-07 07.05.2025r-MainPCB
    sd
2025-05-08 gjvgj
2025-05-08 kjklj
2025-05-09 dfhdfh
2025-05-11 11.05.2025r
2025-05-12 12.05.2025r
2025-05-12 jbjb
2025-06-16 SDFSDFSDF
2025-06-16 coding done v1
2025-06-22 nnm,n
2025-07-20 patch idk which
2025-07-23 oefvoj
2025-07-23 wdads
2025-07-23 dvbdfbdfb
2025-07-24 ghjhbk
2025-07-24 dfbdfb
2025-07-26 buifeebfiifu
2025-07-27 FINIIIISZZZ
2025-07-27 thrsthj
2025-07-27 awdwdawawafwafw
2025-09-11 iiij
2025-09-16 kolejne nwm
2025-09-16 bds b
2025-09-16 1rqwfwr
2025-09-16 affsg
2025-09-16 asdfds
2025-09-16 jgdsfy
2025-09-16 dsfgh
2025-09-22 ikik
2025-10-19 Soft nowy
    wdwf
2025-10-19 werq
